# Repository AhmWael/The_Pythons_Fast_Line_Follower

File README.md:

<div align="center">

# The Pythons Fast Line Follower

### Autonomous Line-Following Robot: Hardware, Firmware, Vision, and Control

</div>

## Overview

This repository contains the design assets and control software for a high-speed autonomous line-following robot. It brings together mechanical CAD, electrical schematics and PCB files, Arduino firmware, camera-based line-following code, and a Bluetooth control application.

## Highlights

- PID-based steering and motor control
- Sensor, camera, and hybrid line-following firmware variants
- Dedicated movement, sensing, and control modules for Arduino
- Mechanical and PCB design files alongside the operational software

## Project Areas

| Area | Contents |
| --- | --- |
| Hardware | PCB board and schematic design files |
| Mechanical | Base-plate and camera-holder STEP models |
| Firmware | Multiple Arduino sketches with movement, sensor-read, and PID-control modules |
| Vision | Python camera line-following scripts |
| Mobile control | MIT App Inventor source and Android APK |

## Repository Structure

```text
.
├── Hardware/                       # Electrical design assets
├── Mechanical/                     # Robot CAD models
└── Software/
    ├── Bluetooth App/              # App Inventor project and APK
    ├── Camera Code/                # Python vision scripts
    └── The_Pythons_.../            # Arduino firmware variants
```

## Firmware Variants

The Arduino projects include sensor-only, camera-assisted, camera-only, and weighted-control variants. The sketches are organized with separate modules for movement, PID calculations, and sensor readings.

Open the intended `.ino` file with Arduino IDE, select the connected board and serial port, then upload. Calibrate sensor thresholds, motor wiring, and PID values for the physical robot before operating it on a track.

## Author

**Youssef Mohamed Attia**  
[GitHub](https://github.com/YoussefMohAttia) · [LinkedIn](https://www.linkedin.com/in/youssefmohattia/)

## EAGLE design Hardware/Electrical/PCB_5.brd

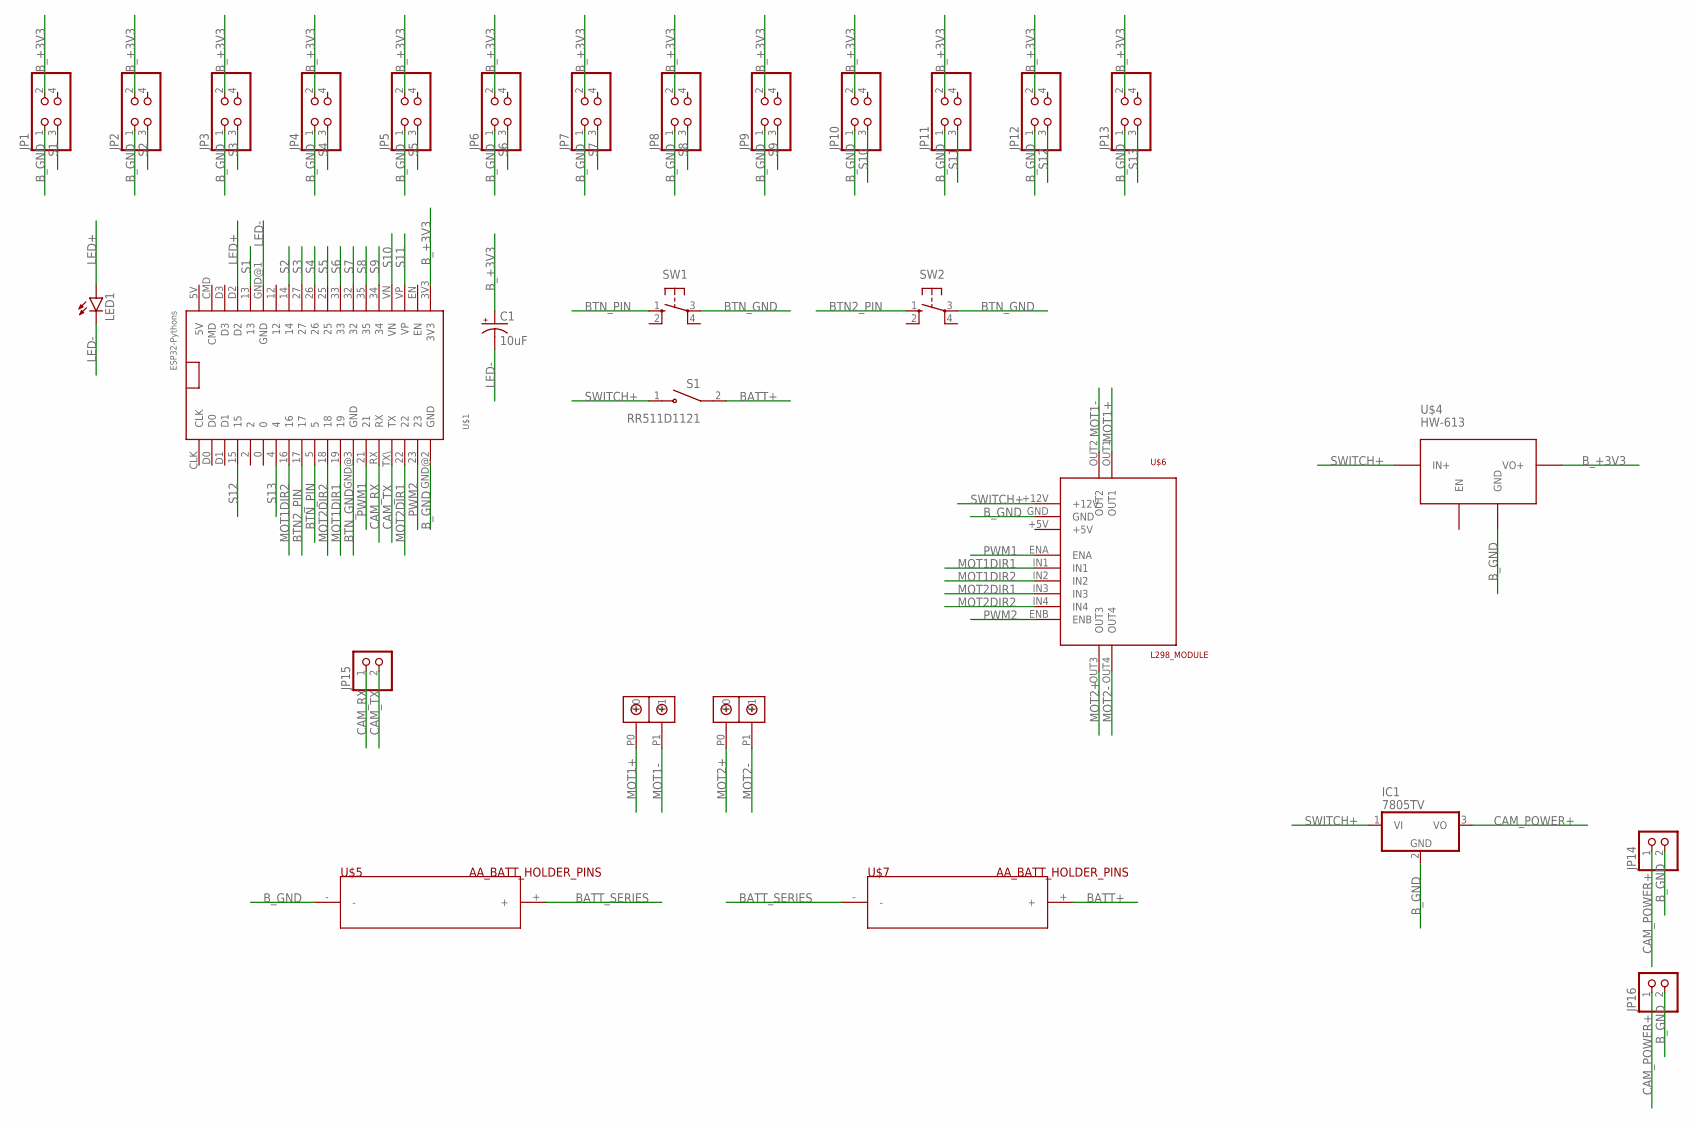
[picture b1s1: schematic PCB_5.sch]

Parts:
C1: 10uF; CPOL-RADIAL-2.5MM-5MM
IC1: 7805TV; TO220V
JP1, JP2, JP3, JP4, JP5, JP6, JP7, JP8, JP9, JP10, JP11, JP12, JP13: PINHD-2X2; 2X02
JP14, JP15, JP16: PINHD-1X2; 1X02
LED1: LED5MM
S1: RR511D1121; E-SWITCH_RR511D1121
SW1, SW2: 10-XX; B3F-10XX
U$1: ESP32DEVKITV1; ESP32-DEVKITV1
U$2, U$3: DBCONN-1X2
U$4: HW-613
U$5, U$7: AA_BATT_HOLDER_PINS
U$6: L298_MODULE

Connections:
BATT+: S1.2 (COM), U$7.+
BATT_SERIES: U$5.+, U$7.-
BTN2_PIN: SW2.1 (S), U$1.17
BTN_GND: SW1.3, SW2.3, U$1.GND@3 (GND)
BTN_PIN: SW1.1 (S), U$1.5
B_+3V3: C1.1 (+), JP1.2, JP2.2, JP3.2, JP4.2, JP5.2, JP6.2, JP7.2, JP8.2, JP9.2, JP10.2, JP11.2, JP12.2, JP13.2, U$1.3V3, U$4.VO+
B_GND: IC1.2 (GND), JP1.1, JP2.1, JP3.1, JP4.1, JP5.1, JP6.1, JP7.1, JP8.1, JP9.1, JP10.1, JP11.1, JP12.1, JP13.1, JP14.2, JP16.2, U$1.GND@2 (GND), U$4.GND, U$5.-, U$6.GND
CAM_POWER+: IC1.3 (VO), JP14.1, JP16.1
CAM_RX: JP15.1, U$1.RX
CAM_TX: JP15.2, U$1.TX\ (TX)
LED+: LED1.A, U$1.D2
LED-: C1.2 (-), LED1.K (C), U$1.GND@1 (GND)
MOT1+: U$2.P0, U$6.OUT1
MOT1-: U$2.P1, U$6.OUT2
MOT1DIR1: U$1.19, U$6.IN1
MOT1DIR2: U$1.16, U$6.IN2
MOT2+: U$3.P0, U$6.OUT3
MOT2-: U$3.P1, U$6.OUT4
MOT2DIR1: U$1.22, U$6.IN3
MOT2DIR2: U$1.18, U$6.IN4
PWM1: U$1.21, U$6.ENA
PWM2: U$1.23, U$6.ENB
S1: JP1.3, U$1.13
S2: JP2.3, U$1.14
S3: JP3.3, U$1.27
S4: JP4.3, U$1.26
S5: JP5.3, U$1.25
S6: JP6.3, U$1.33
S7: JP7.3, U$1.32
S8: JP8.3, U$1.35
S9: JP9.3, U$1.34
S10: JP10.3, U$1.VN
S11: JP11.3, U$1.VP
S12: JP12.3, U$1.15
S13: JP13.3, U$1.4
SWITCH+: IC1.1 (VI), S1.1 (NO), U$4.IN+, U$6.+12V

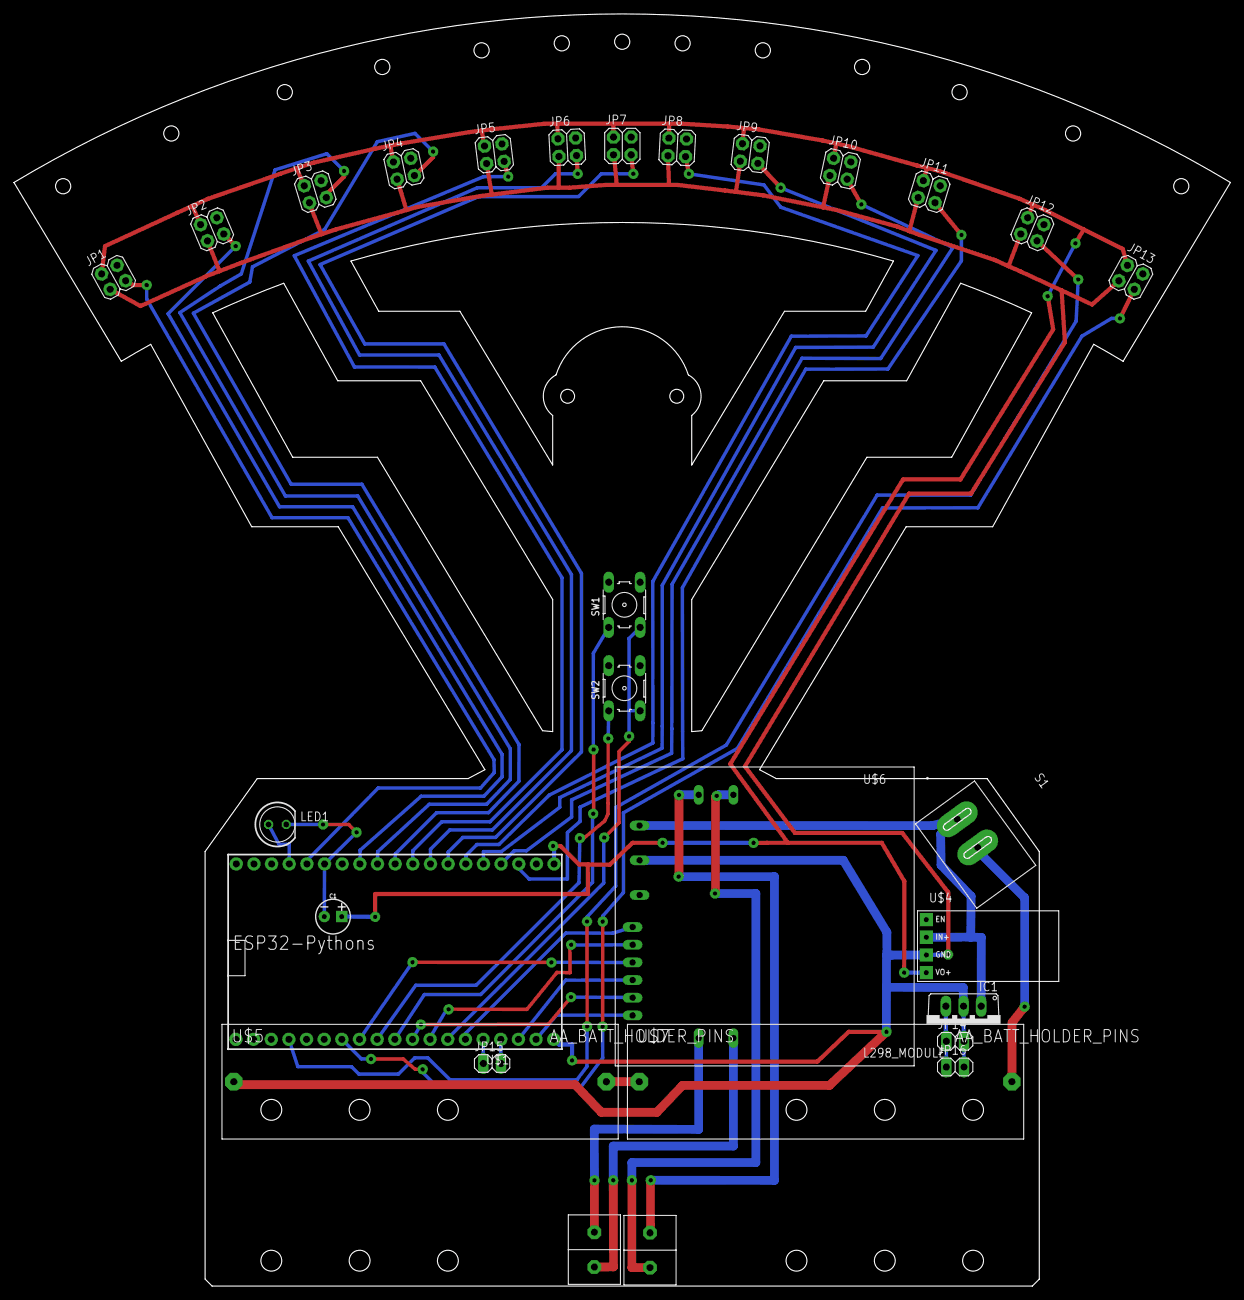
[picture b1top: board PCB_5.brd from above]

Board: 2 copper layers, 175.0 x 183.0 mm, 29 parts (0 on the bottom side), 36 nets.

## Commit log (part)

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2024-08-21 Added PCB Design 1
2024-08-29 Added latest hardware designs
2024-08-30 Added ESP32 Code
2024-08-31 Added Line Sensor Calibration
    - Added map function to map each sensor reading to a range of 0-1000
    - Added Calibration function to get minimum and maximum readings of sensors from each sensor
2024-08-31 Added button to start calibration
2024-09-01 Fixed some bugs in sensor read function and calibration
2024-09-02 first test sh8al
    removed last 2 corner sensors
    edited base speed
    editied kp value
2024-09-04 First version bluetooth Code
2024-09-05 Added Bluetooth app
2024-09-05 Before Changing PID Function
2024-09-07 Discrete Code & Weights & BT
    Main Code discrete+ Code with Weights + Bluetooth without weights
2024-09-07 Added the updated Bluetooth App
    Added Weights + Enhanced UI
2024-09-07 Added some optimization to the code
2024-09-10 Added backward & stop functionality and auto calibration
2024-09-11 Changed debug to #define
2024-09-11 Updated bluetooth app
2024-09-12 Updated hardware files
2024-09-12 Changed Black/White threshold Calculation
    Automatic Calculation of Black and White Threshold based on average of both values
2024-09-13 Changed motor pins & fixed stop function
2024-09-13 Updated pins
2024-09-13 Returned to the old threshold 700
2024-09-16 Added Separate Arduino Camera Code + Python code
    Camera guiding robot on curves and straight lines
2024-09-17 Bluetooth + Camera updates
    Updated Bluetooth app to add camera parameters control.
    Updated Arduino code with camera to receive the arguments from the bluetooth app
    Updated Camera python code
    Added a separate code for line tracking with camera only
2024-09-17 added last_case in camera+ stop before slow down
2024-09-19 Added calibration speed variable & fixed values for backward and stop
2024-09-22 Added adjust backspeed with sensor line position
2024-09-22 Added debug for each section
2024-09-23 Edited Backward Functions condition
2024-09-25 Added Start Button + Camera Code Enhancements
    - Added the event of pushbutton to start at speed of 225 ( to be edited later)
    - Camera Line following break when last 2 IRs detected black
    - Added constraints for upper region
    - Added middle region position when upper region and lower region not detected
2024-09-26 Enhanced Camera Code
    Using the first and last regions only for guidance
2024-09-27 Camera Code edit
    -Changed crop and region values
    -Line deflection depends on the top region only
2024-09-28 last
2024-09-28 camera
2024-09-30 Updated hardware
2024-10-01 Minor modification in values of main code and camera python script
    -Changed threshold, contrast and brightness for camera
    -Increased delay for curves in main code
2024-10-01 Updated Bluetooth App
    Edited Bluetooth device address for new ESP32
2024-10-01 Updated bluetooth app
    -Solved bug that assign null value to variables when text is empty

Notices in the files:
parts and their libraries:
SparkFun-Capacitors: Licensing: Creative Commons ShareAlike 4.0 International - https://creativecommons.org/licenses/by-sa/4.0
